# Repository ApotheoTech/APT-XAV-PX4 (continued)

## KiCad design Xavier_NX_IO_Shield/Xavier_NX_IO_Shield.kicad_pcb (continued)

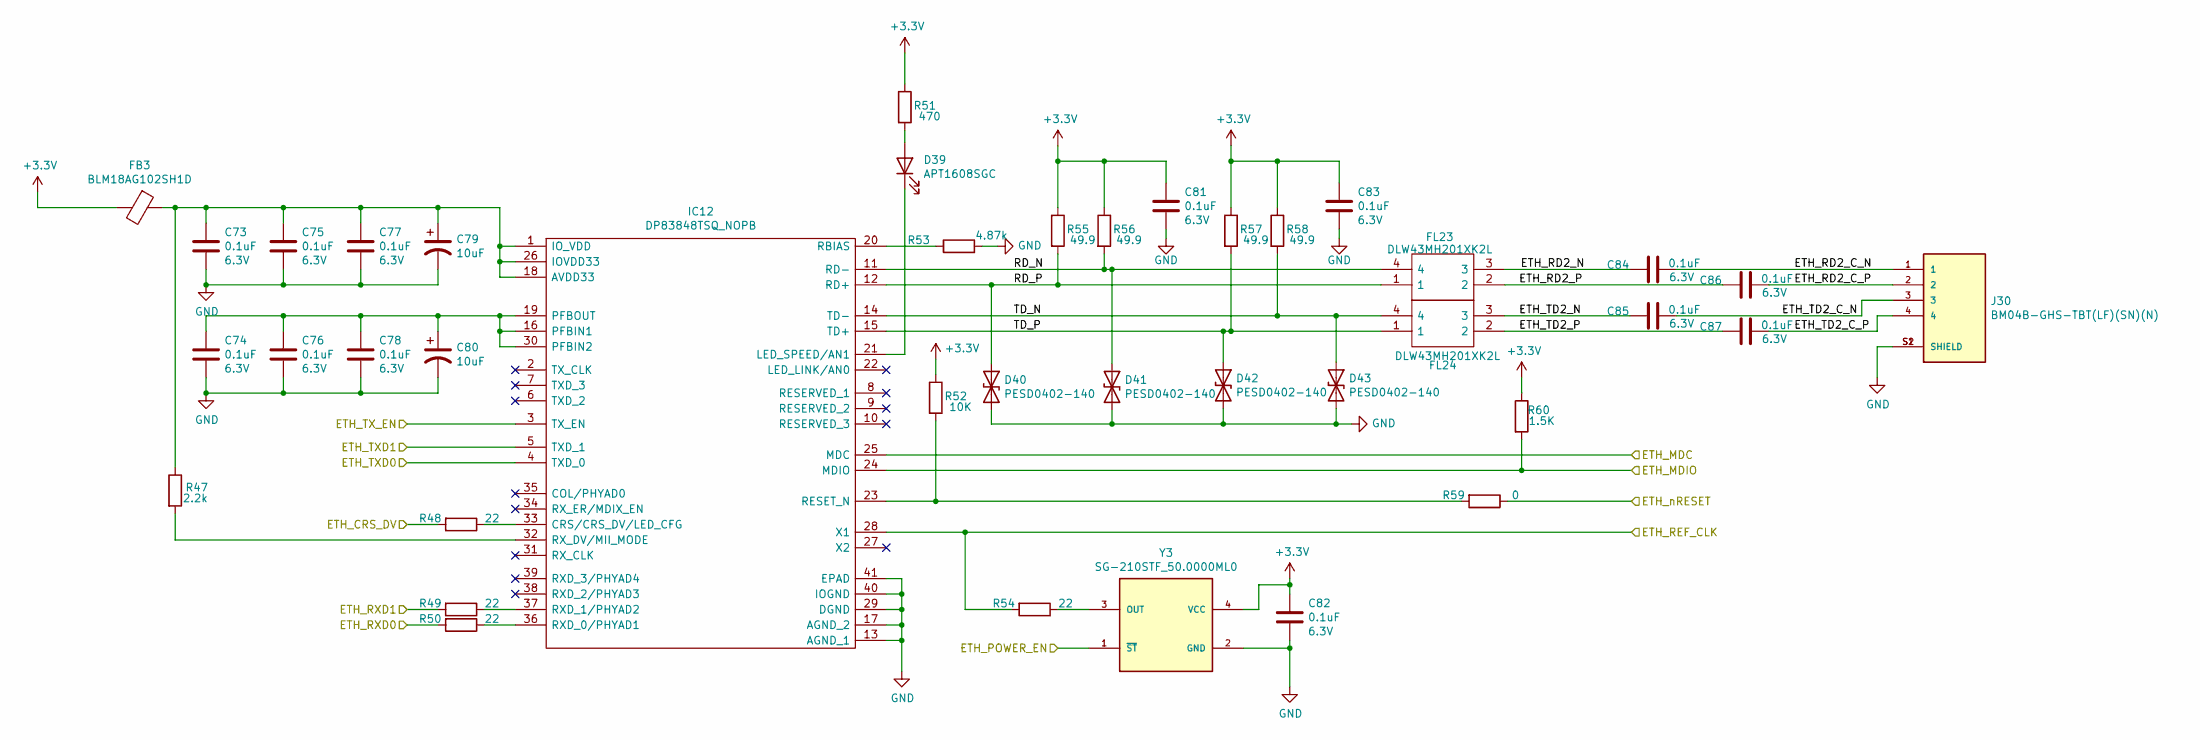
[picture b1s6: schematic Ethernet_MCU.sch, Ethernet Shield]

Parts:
C73, C74, C75, C76, C77, C78, C81, C82, C83, C84, C85, C86, C87: 0.1uF; C_0402_1005Metric; Voltage 6.3V; PartNumber C1005X5R0J104K050BA
C79, C80: 10uF; CP_EIA-1608-10_AVX-L; Voltage 10V; PartNumber F381A106MMAAH1
D39: APT1608SGC; LED_0603_1608Metric
D40, D41, D42, D43: PESD0402-140; PESD0402
FB3: ‎BLM18AG102SH1D‎; D_0603_1608Metric
FL23, FL24: DLW43MH201XK2L; DLW43MH201XK2K; Mouser Part Number 81-DLW43MH201XK2L
IC12: DP83848TSQ_NOPB; DP83848TSQ; Mouser Part Number 926-DP83848TSQ/NOPB
J30: BM04B-GHS-TBT(LF)(SN)(N); PARTREV N/A
R47: 2.2k; R_0402_1005Metric; PartNumber ERJ-2RKF2201X
R48, R49, R50, R54: 22; R_0402_1005Metric; PartNumber CRCW040222R0FKEDC
R51: 470; R_0402_1005Metric; PartNumber CRCW0402470RFKEDC
R52: 10K; R_0402_1005Metric; PartNumber ERJ-2RKF1002X
R53: 4.87k; R_0402_1005Metric; PartNumber ERJ-2RKF4871X
R55, R56, R57, R58: 49.9; R_0402_1005Metric; PartNumber ERJ-2RKF49R9X
R59: 0; R_0402_1005Metric; PartNumber CRCW04020000Z0EDHP
R60: 1.5K; R_0402_1005Metric; PartNumber ERJ-2RKF1501X
Y3: SG-210STF_50.0000ML0; SG-210STF_50ML0; PARTREV N/A

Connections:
+3V3: C81.1, C82.1, C83.1, FB3.2, R51.1, R52.1, R55.1, R56.1, R57.1, R58.1, R60.1, Y3.4 (VCC); also elsewhere on the board
/ETH_CRS_DV: R48.2; also elsewhere on the board
/ETH_MDC: IC12.25 (MDC); also elsewhere on the board
/ETH_MDIO: IC12.24 (MDIO), R60.2; also elsewhere on the board
/ETH_POWER_EN: Y3.1 (~ST); also elsewhere on the board
/ETH_REF_CLK: IC12.28 (X1), R54.2; also elsewhere on the board
/ETH_RXD0: R50.2; also elsewhere on the board
/ETH_RXD1: R49.2; also elsewhere on the board
/ETH_TXD0: IC12.4 (TXD_0); also elsewhere on the board
/ETH_TXD1: IC12.5 (TXD_1); also elsewhere on the board
/ETH_TX_EN: IC12.3 (TX_EN); also elsewhere on the board
/Ethernet Microcontroller/ETH_RD2_C_N: C84.2, J30.1
/Ethernet Microcontroller/ETH_RD2_C_P: C86.2, J30.2
/Ethernet Microcontroller/ETH_RD2_N: C84.1, FL23.3
/Ethernet Microcontroller/ETH_RD2_P: C86.1, FL23.2
/Ethernet Microcontroller/ETH_TD2_C_N: C85.2, J30.3
/Ethernet Microcontroller/ETH_TD2_C_P: C87.2, J30.4
/Ethernet Microcontroller/ETH_TD2_N: C85.1, FL24.3
/Ethernet Microcontroller/ETH_TD2_P: C87.1, FL24.2
/Ethernet Microcontroller/RD_N: D41.1 (A1), FL23.4, IC12.11 (RD-), R56.2
/Ethernet Microcontroller/RD_P: D40.1 (A1), FL23.1, IC12.12 (RD+), R55.2
/Ethernet Microcontroller/TD_N: D43.1 (A1), FL24.4, IC12.14 (TD-), R58.2
/Ethernet Microcontroller/TD_P: D42.1 (A1), FL24.1, IC12.15 (TD+), R57.2
/PG6: R59.1; also elsewhere on the board
GND: C73.2, C74.2, C75.2, C76.2, C77.2, C78.2, C79.2, C80.2, C81.2, C82.2, C83.2, D40.2 (A2), D41.2 (A2), D42.2 (A2), D43.2 (A2), IC12.13 (AGND_1), IC12.17 (AGND_2), IC12.29 (DGND), IC12.40 (IOGND), IC12.41 (EPAD), J30.S1 (SHIELD), J30.S2 (SHIELD), R53.2, Y3.2 (GND); also elsewhere on the board
unnamed: C73.1, C75.1, C77.1, C79.1, FB3.1, IC12.1 (IO_VDD), IC12.18 (AVDD33), IC12.26 (IOVDD33), R47.1
unnamed: C74.1, C76.1, C78.1, C80.1, IC12.16 (PFBIN1), IC12.19 (PFBOUT), IC12.30 (PFBIN2)
unnamed: D39.1 (K), IC12.21 (LED_SPEED/AN1)
unnamed: D39.2 (A), R51.2
unnamed: IC12.20 (RBIAS), R53.1
unnamed: IC12.23 (RESET_N), R52.2, R59.2
unnamed: IC12.32 (RX_DV/MII_MODE), R47.2
unnamed: IC12.33 (CRS/CRS_DV/LED_CFG), R48.1
unnamed: IC12.36 (RXD_0/PHYAD1), R50.1
unnamed: IC12.37 (RXD_1/PHYAD2), R49.1
unnamed: R54.1, Y3.3 (OUT)

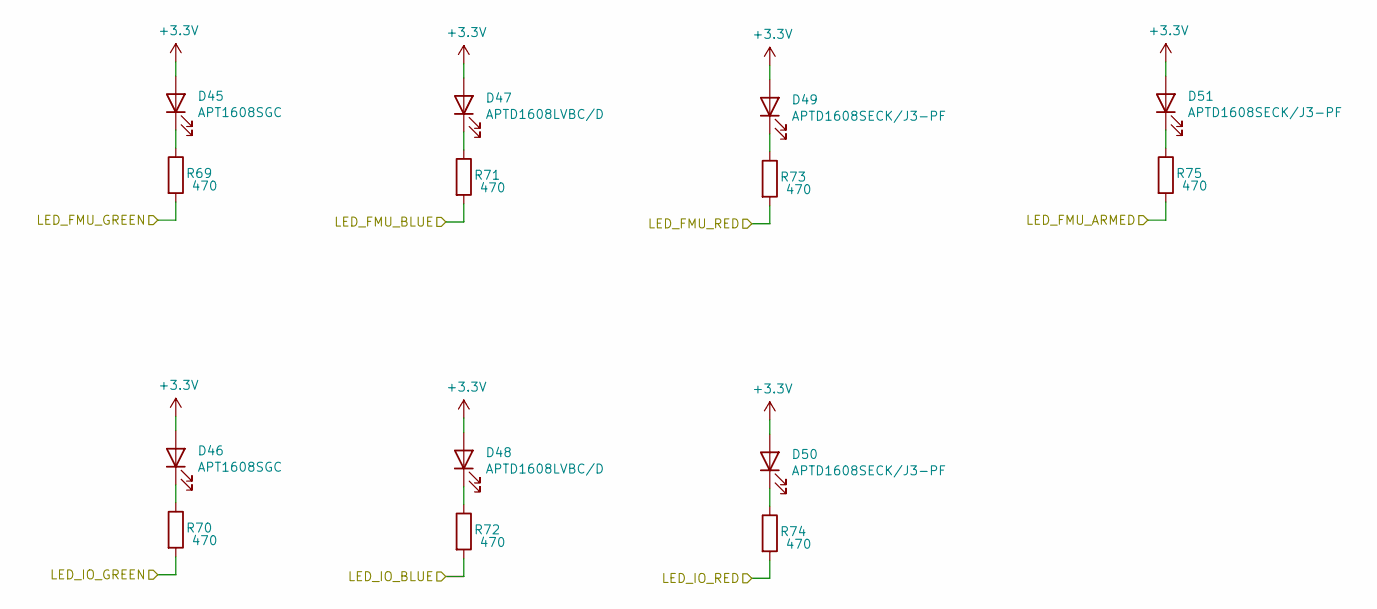
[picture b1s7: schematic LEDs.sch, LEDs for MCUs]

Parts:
D45, D46: APT1608SGC; LED_0603_1608Metric
D47, D48: APTD1608LVBC/D; LED_0603_1608Metric
D49, D50, D51: APTD1608SECK/J3-PF; LED_0603_1608Metric
R69, R70, R71, R72, R73, R74, R75: 470; R_0402_1005Metric; PartNumber CRCW0402470RFKEDC

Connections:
+3V3: D45.2 (A), D46.2 (A), D47.2 (A), D48.2 (A), D49.2 (A), D50.2 (A), D51.2 (A); also elsewhere on the board
/IO_LEDA: R70.2; also elsewhere on the board
/IO_LEDB: R72.2; also elsewhere on the board
/IO_LEDC: R74.2; also elsewhere on the board
/nARMED: R75.2; also elsewhere on the board
/nLED_BLUE: R71.2; also elsewhere on the board
/nLED_GREEN: R69.2; also elsewhere on the board
/nLED_RED: R73.2; also elsewhere on the board
unnamed: D45.1 (K), R69.1
unnamed: D46.1 (K), R70.1
unnamed: D47.1 (K), R71.1
unnamed: D48.1 (K), R72.1
unnamed: D49.1 (K), R73.1
unnamed: D50.1 (K), R74.1
unnamed: D51.1 (K), R75.1

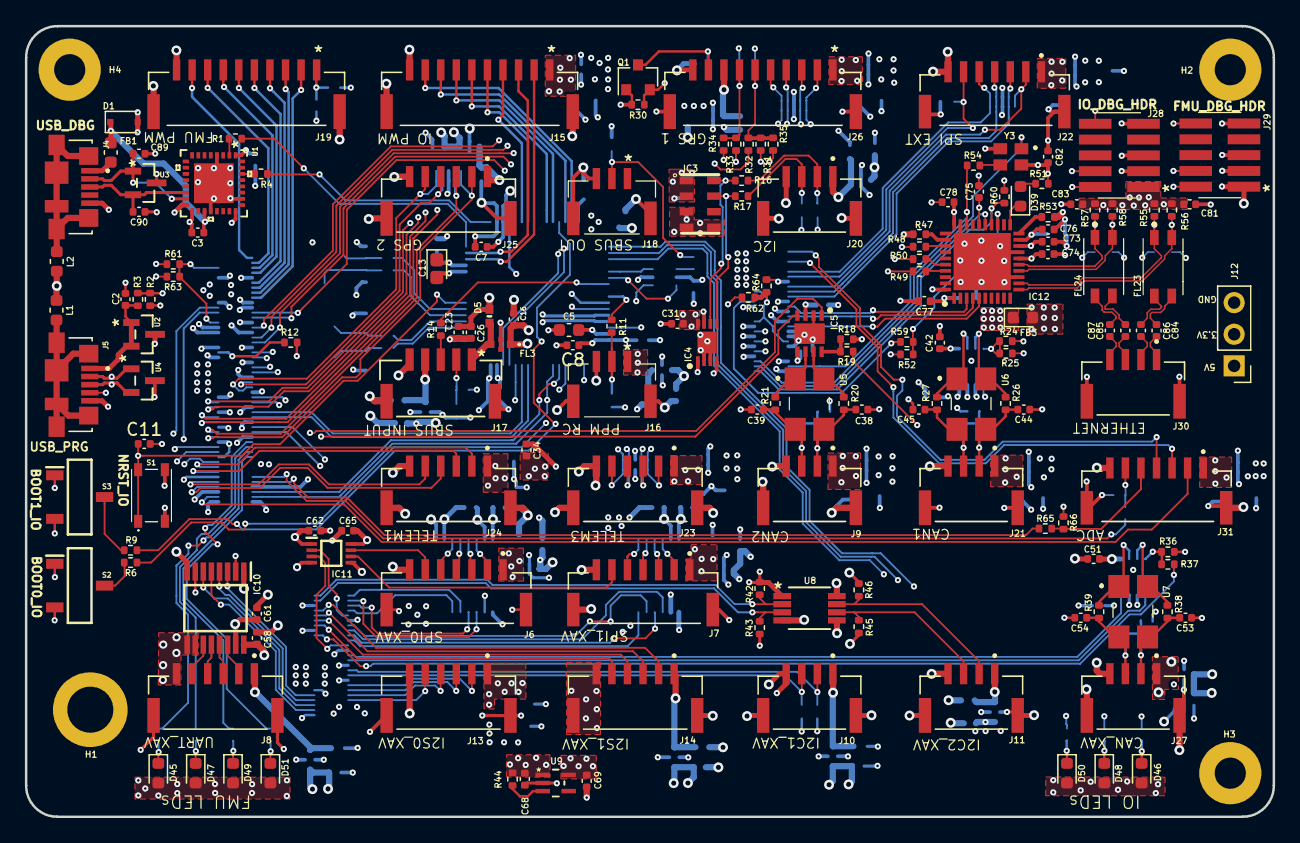
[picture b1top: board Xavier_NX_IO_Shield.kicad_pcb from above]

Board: 6 copper layers, 100.2 x 63.5 mm, 309 parts (0 on the bottom side), 256 nets.

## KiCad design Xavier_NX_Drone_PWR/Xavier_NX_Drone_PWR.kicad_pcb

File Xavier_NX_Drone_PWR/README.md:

# APT-XAV-PX4 Drone Power
Copyright 2022 ApotheoTech LLC

# Description

APT-XAV-PX4 Drone Power board is meant to be soldered onto a connector to a LiPo battery, like the HolyBro PixHawk 4 Power supply board. It is untested.

# Where to Buy

The prototypes for this board were not built due to a combination of a lack of funds, and a redirection of focus to another project February of 2021. If you are interested in supporting the project, or wish to create the prototypes, I have most of the BOM in stock. 

For inquires email me at chance189[at]knights.ucf.edu

# Referenced Works
* [PX4 Hardware](https://github.com/pixhawk/Hardware)

# Licensing

Released under the GPLV3 License.

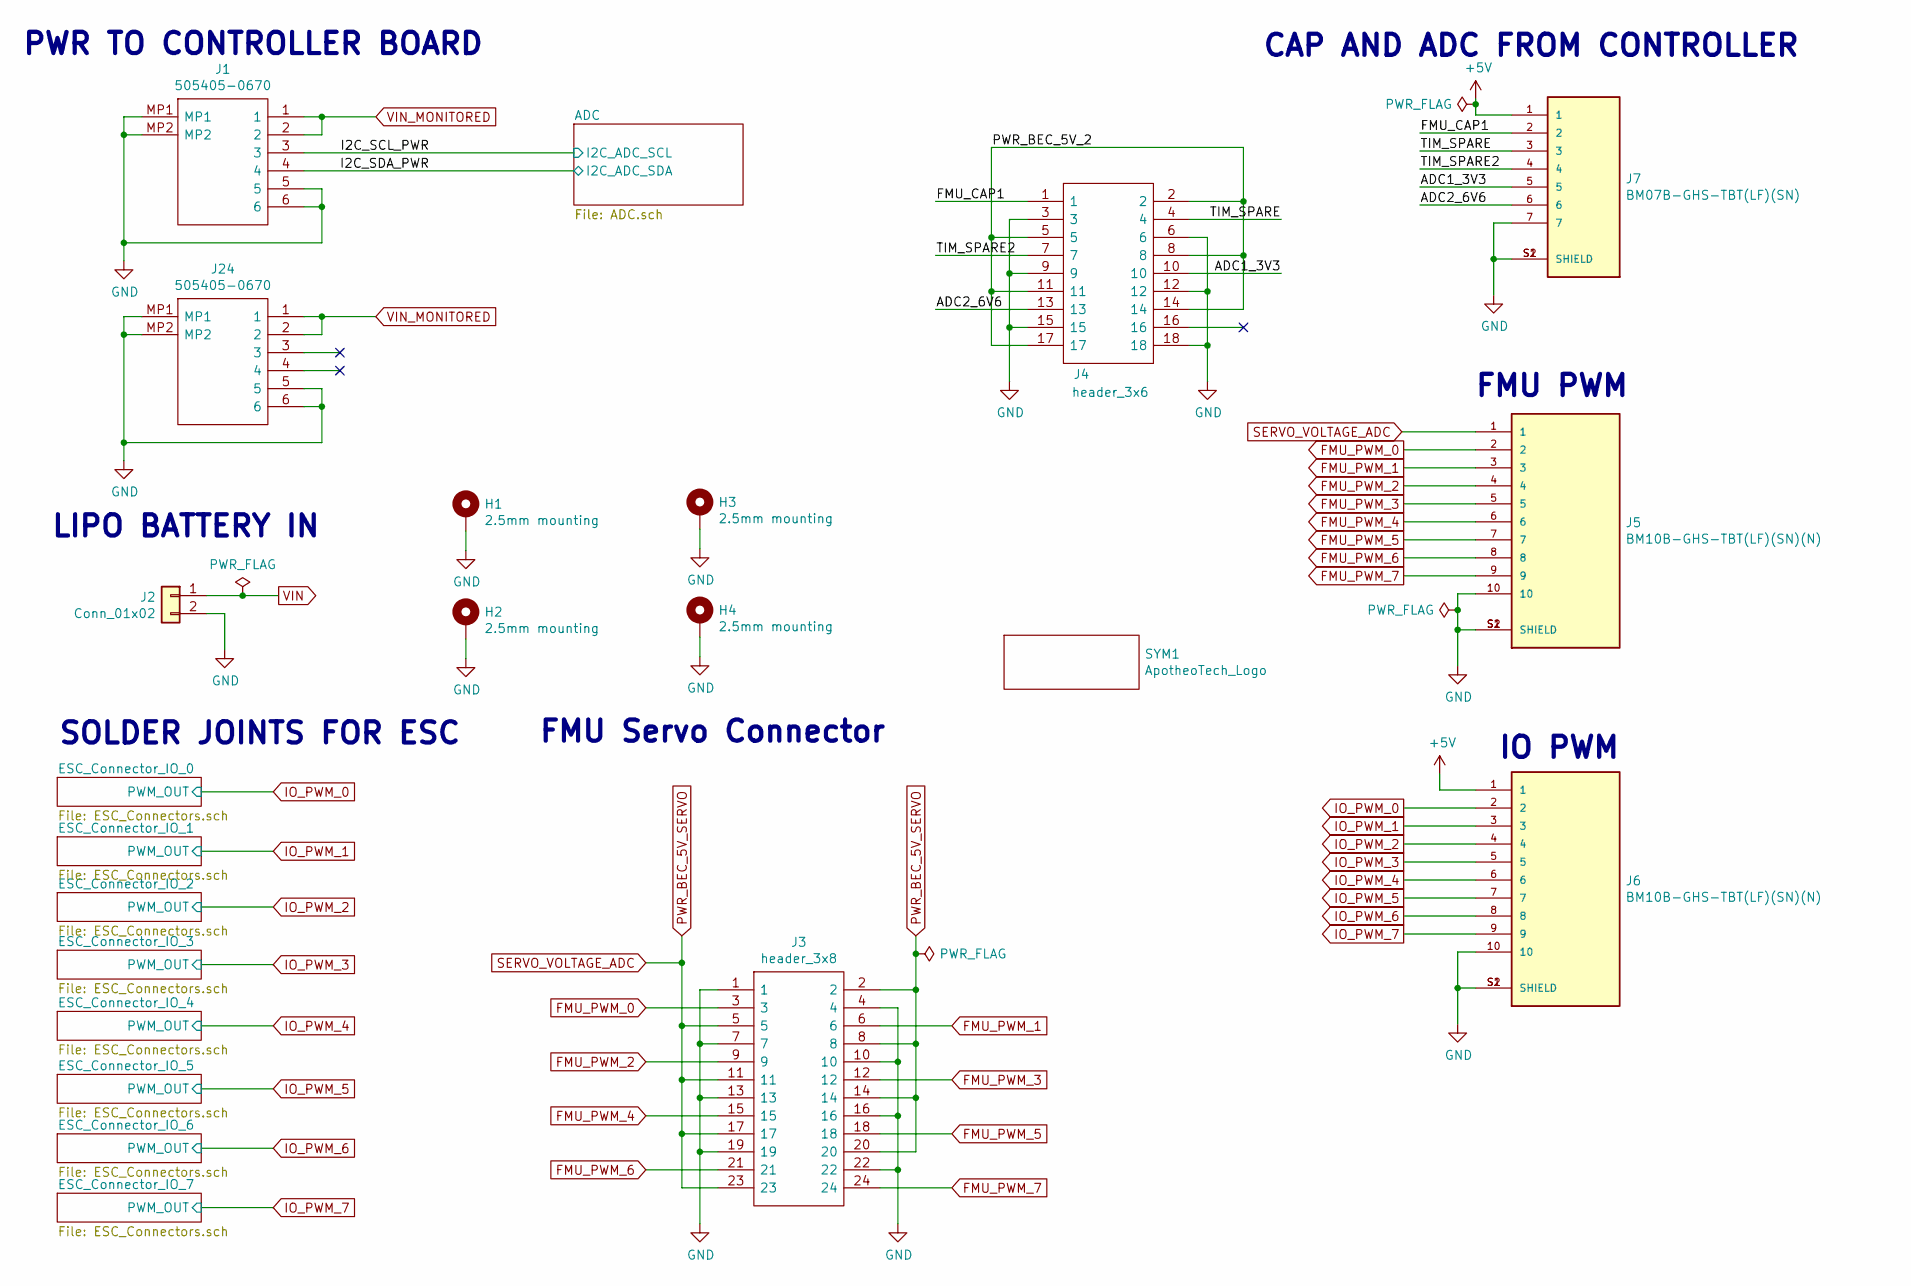
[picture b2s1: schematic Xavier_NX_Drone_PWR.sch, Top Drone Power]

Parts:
H1, H2, H3, H4: 2.5mm mounting; MountingHole_2.5mm_Pad
J1, J24: 505405-0670; 5054050670; Mouser Part Number 538-505405-0670
J2: Conn_01x02; BAT_SOLDER_JOINT
J3: header_3x8; Manufacturer_Part_Number TSW-108-25-L-T-RA
J4: header_3x6; Mouser Part Number 200-TSW10610TTRA
J5, J6: BM10B-GHS-TBT(LF)(SN)(N); PARTREV N/A
J7: BM07B-GHS-TBT(LF)(SN); PARTREV NA
SYM1: ApotheoTech_Logo; ApotheoTech_Sym

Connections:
+5V: J6.1, J7.1; also elsewhere on the board
/ADC1_3V3: J4.10, J7.5
/ADC2_6V6: J4.13, J7.6
/FMU_CAP1: J4.1, J7.2
/I2C_SCL_PWR: J1.3; also elsewhere on the board
/I2C_SDA_PWR: J1.4; also elsewhere on the board
/PWR_BEC_5V_2: J4.2, J4.5, J4.8, J4.11, J4.14, J4.17
/TIM_SPARE: J4.4, J7.3
/TIM_SPARE2: J4.7, J7.4
FMU_PWM_0: J3.3, J5.2
FMU_PWM_1: J3.6, J5.3
FMU_PWM_2: J3.9, J5.4
FMU_PWM_3: J3.12, J5.5
FMU_PWM_4: J3.15, J5.6
FMU_PWM_5: J3.18, J5.7
FMU_PWM_6: J3.21, J5.8
FMU_PWM_7: J3.24, J5.9
GND: H1.1, H2.1, H3.1, H4.1, J1.5, J1.6, J1.MP1, J1.MP2, J2.2, J3.1, J3.4, J3.7, J3.10, J3.13, J3.16, J3.19, J3.22, J4.3, J4.6, J4.9, J4.12, J4.15, J4.18, J5.10, J5.S1 (SHIELD), J5.S2 (SHIELD), J6.10, J6.S1 (SHIELD), J6.S2 (SHIELD), J7.7, J7.S1 (SHIELD), J7.S2 (SHIELD), J24.5, J24.6, J24.MP1, J24.MP2; also elsewhere on the board
IO_PWM_0: J6.2; also elsewhere on the board
IO_PWM_1: J6.3; also elsewhere on the board
IO_PWM_2: J6.4; also elsewhere on the board
IO_PWM_3: J6.5; also elsewhere on the board
IO_PWM_4: J6.6; also elsewhere on the board
IO_PWM_5: J6.7; also elsewhere on the board
IO_PWM_6: J6.8; also elsewhere on the board
IO_PWM_7: J6.9; also elsewhere on the board
PWR_BEC_5V_SERVO: J3.2, J3.5, J3.8, J3.11, J3.14, J3.17, J3.20, J3.23, J5.1
VIN: J2.1; also elsewhere on the board
VIN_MONITORED: J1.1, J1.2, J24.1, J24.2; also elsewhere on the board

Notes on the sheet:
PWR TO CONTROLLER BOARD
LIPO BATTERY IN
CAP AND ADC FROM CONTROLLER
FMU PWM
IO PWM
SOLDER JOINTS FOR ESC
FMU Servo Connector

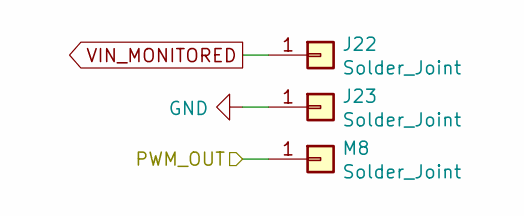
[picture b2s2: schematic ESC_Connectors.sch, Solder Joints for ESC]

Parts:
J8, J9: Solder_Joint; Solder_Joint_PWR
M1: Solder_Joint; PWM_Solder_Joint

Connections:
GND: J9.1; also elsewhere on the board
IO_PWM_0: M1.1; also elsewhere on the board
VIN_MONITORED: J8.1; also elsewhere on the board

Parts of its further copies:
J10, J11, J12, J13, J14, J15, J16, J17, J18, J19, J20, J21, J22, J23: Solder_Joint; Solder_Joint_PWR
M2, M3, M4, M5, M6, M7, M8: Solder_Joint; PWM_Solder_Joint

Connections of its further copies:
GND: J11.1, J13.1, J15.1, J17.1, J19.1, J21.1, J23.1; also elsewhere on the board
IO_PWM_1: M2.1; also elsewhere on the board
IO_PWM_2: M3.1; also elsewhere on the board
IO_PWM_3: M4.1; also elsewhere on the board
IO_PWM_4: M5.1; also elsewhere on the board
IO_PWM_5: M6.1; also elsewhere on the board
IO_PWM_6: M7.1; also elsewhere on the board
IO_PWM_7: M8.1; also elsewhere on the board
VIN_MONITORED: J10.1, J12.1, J14.1, J16.1, J18.1, J20.1, J22.1; also elsewhere on the board

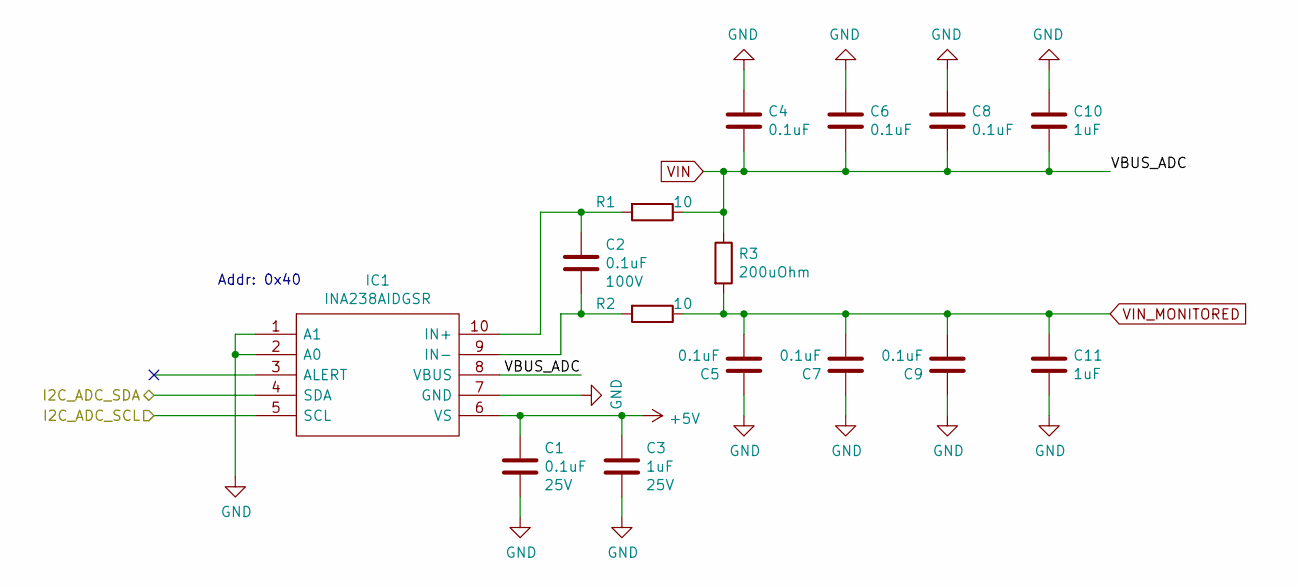
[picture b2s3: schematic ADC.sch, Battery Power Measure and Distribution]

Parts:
C1: 0.1uF; R_0402_1005Metric; Voltage 25V; PartNumber ‎GCM155R71E104KE02D‎
C2, C4, C5, C6, C7, C8, C9: 0.1uF; R_0805_2012Metric; Voltage 100V; PartNumber ‎08051C104J4T2A
C3: 1uF; R_0402_1005Metric; Voltage 25V; PartNumber ‎GRT155R61E105KE01D‎
C10, C11: 1uF; R_1206_3216Metric; Voltage 100V; PartNumber ‎12061C105KAT2A‎
IC1: INA238AIDGSR; Mouser Part Number 595-INA238AIDGSR
R1, R2: 10; R_0402_1005Metric; PartNumber RCS040210R0FKED
R3: 200uOhm; PU5931FKHPA0U2L; PartNumber PU5931FKHPA0U2L

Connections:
+5V: C1.1, C3.1, IC1.6 (VS); also elsewhere on the board
/I2C_SCL_PWR: IC1.5 (SCL); also elsewhere on the board
/I2C_SDA_PWR: IC1.4 (SDA); also elsewhere on the board
GND: C1.2, C3.2, C4.1, C5.1, C6.1, C7.1, C8.1, C9.1, C10.1, C11.2, IC1.1 (A1), IC1.2 (A0), IC1.7 (GND); also elsewhere on the board
unnamed: C2.1, IC1.10 (IN+), R1.2
unnamed: C2.2, IC1.9 (IN-), R2.2
VIN: C4.2, C6.2, C8.2, C10.2, IC1.8 (VBUS), R1.1, R3.1; also elsewhere on the board
VIN_MONITORED: C5.2, C7.2, C9.2, C11.1, R2.1, R3.2; also elsewhere on the board

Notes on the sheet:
Addr: 0x40

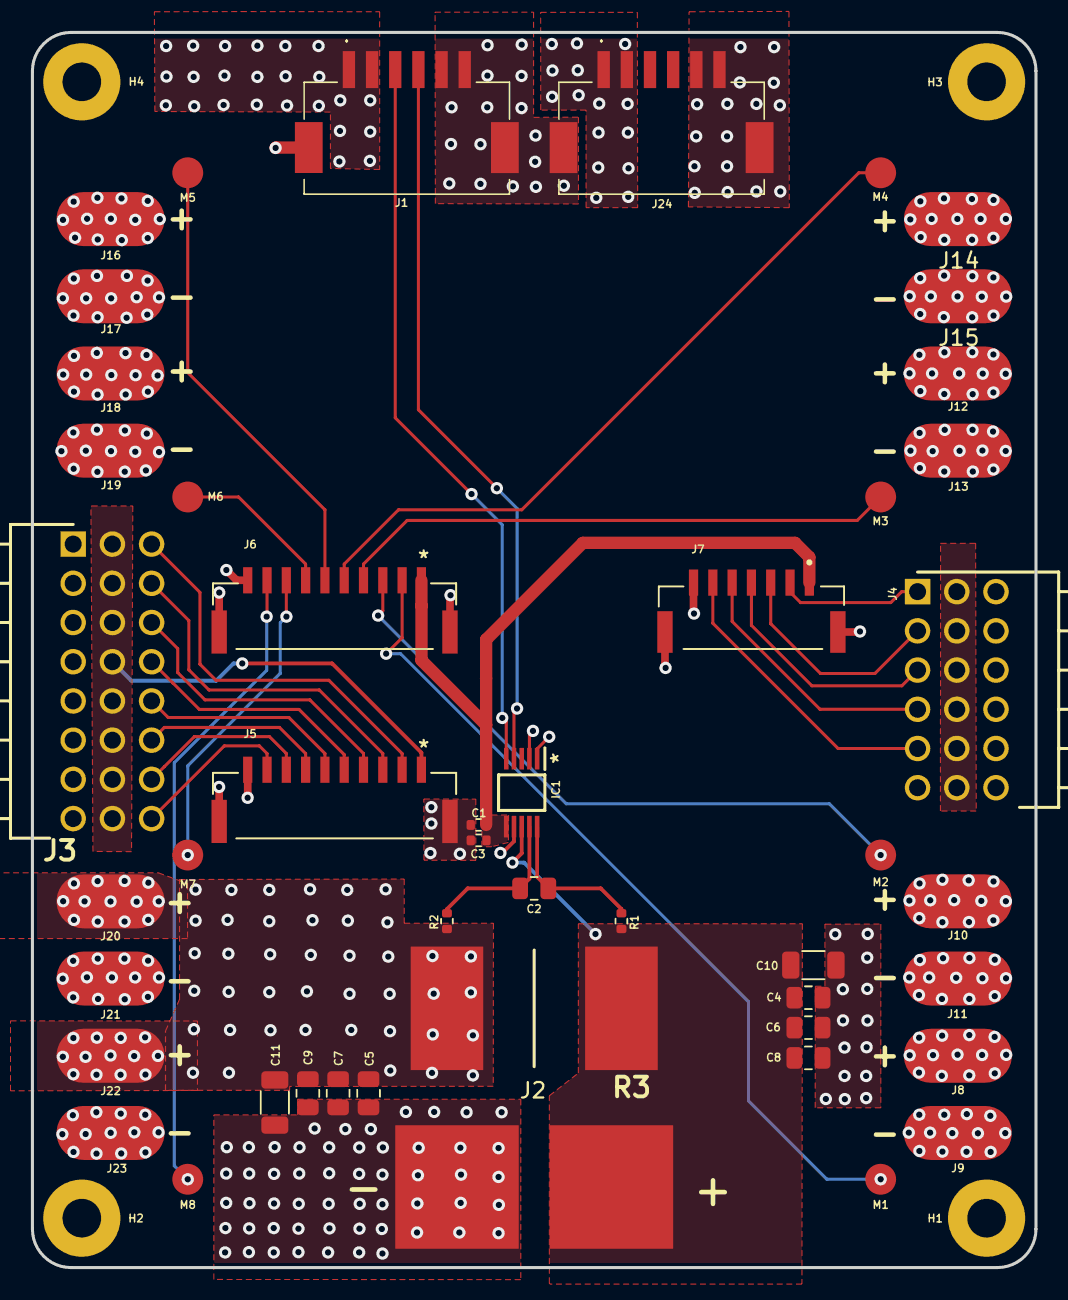
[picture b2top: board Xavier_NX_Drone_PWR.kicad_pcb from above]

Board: 6 copper layers, 65.0 x 80.0 mm, 52 parts (0 on the bottom side), 31 nets.

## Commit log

2022-02-13 Init Board Files
2022-02-13 Readme test
2022-02-13 Add Readmes to each page
2022-02-13 Add video
